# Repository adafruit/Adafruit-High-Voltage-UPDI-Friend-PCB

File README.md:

## Adafruit High Voltage UPDI Friend - USB Serial UPDI Programmer PCB

<a href="http://www.adafruit.com/products/5893"><br/>
Click here to purchase one from the Adafruit shop</a>

PCB files for the Adafruit High Voltage UPDI Friend - USB Serial UPDI Programmer. 

Format is EagleCAD schematic and board layout
* https://www.adafruit.com/product/5893

### Description

UPDI stands for Unified Program and Debug Interface, but this board is so smol and cute that we will call it the Unusually Playful Device Interfacer and pat its head when it does a good job. It's designed to make programming modern ATtiny chips very easy because it has 3V or 5V power and logic select, power, and transmit indicator LEDs, and a quick cable for poking into a breadboard.

Unlike our simple UPDI version, this board is HV for High Voltage because it will let you send a quick 12V pulse to the UPDI like right before programming. This is required for when the chip is configured to use the UPDI pin as a reset or GPIO. This board will also let you 'unbrick' any chip configured for HV usage, you can use it to reset the fuses for Low Voltage programming.

As for our seesaw boards, we have been working a lot with ATtiny816, ATtiny817, and ATtiny1616 chips lately. And we're often needing to program them with a CP2102-based breakout with a 1K resistor soldered between the RX and TX pins. But we were hankering for a nicer programmer!

This UPDI High Voltage Friend makes programming such chips very easy:

* Select between 3V or 5V power and logic - the 3V regulator can source up to 500mA to run even big projects. 
* Internal 12V boost converter with analog switch that will send a pulse to the UPDI line when the RTS pin is toggled low. 
* CH340E USB Serial converter chip with cross-platform drivers
* 1K Loop-back Resistor between RX and TX
* USB Type C for data and power connection to any computer
* JST SH cable included for quick plugging into a breadboard - you can get another JST SH 3-pin cable with sockets or with pin header here.
* 0.1" spaced breakout holes for custom connections.
* Green power OK LED
* Red serial activity LED
* Inspired by this [open-source hardware design](https://github.com/wagiminator/AVR-Programmer/tree/master/SerialUPDI_HV_Programmer) from [Stefan Wagner](https://github.com/wagiminator)!

We use Arduino IDE with the megaTinyCore board support package installed; simply select "Serial UPDI" as the programmer type. We use 230Kbps, but 56Kbps is also good. In order to enable the high-voltage fuses settings, you'll need to edit boards.txt to remove the # comment tag on the “UPDI/RESET PIN CONFIGURATION” lines.
### License

Adafruit invests time and resources providing this open source design, please support Adafruit and open-source hardware by purchasing products from [Adafruit](https://www.adafruit.com)!

Designed by Limor Fried/Ladyada for Adafruit Industries.

Creative Commons Attribution/Share-Alike, all text above must be included in any redistribution. 
See license.txt for additional details.

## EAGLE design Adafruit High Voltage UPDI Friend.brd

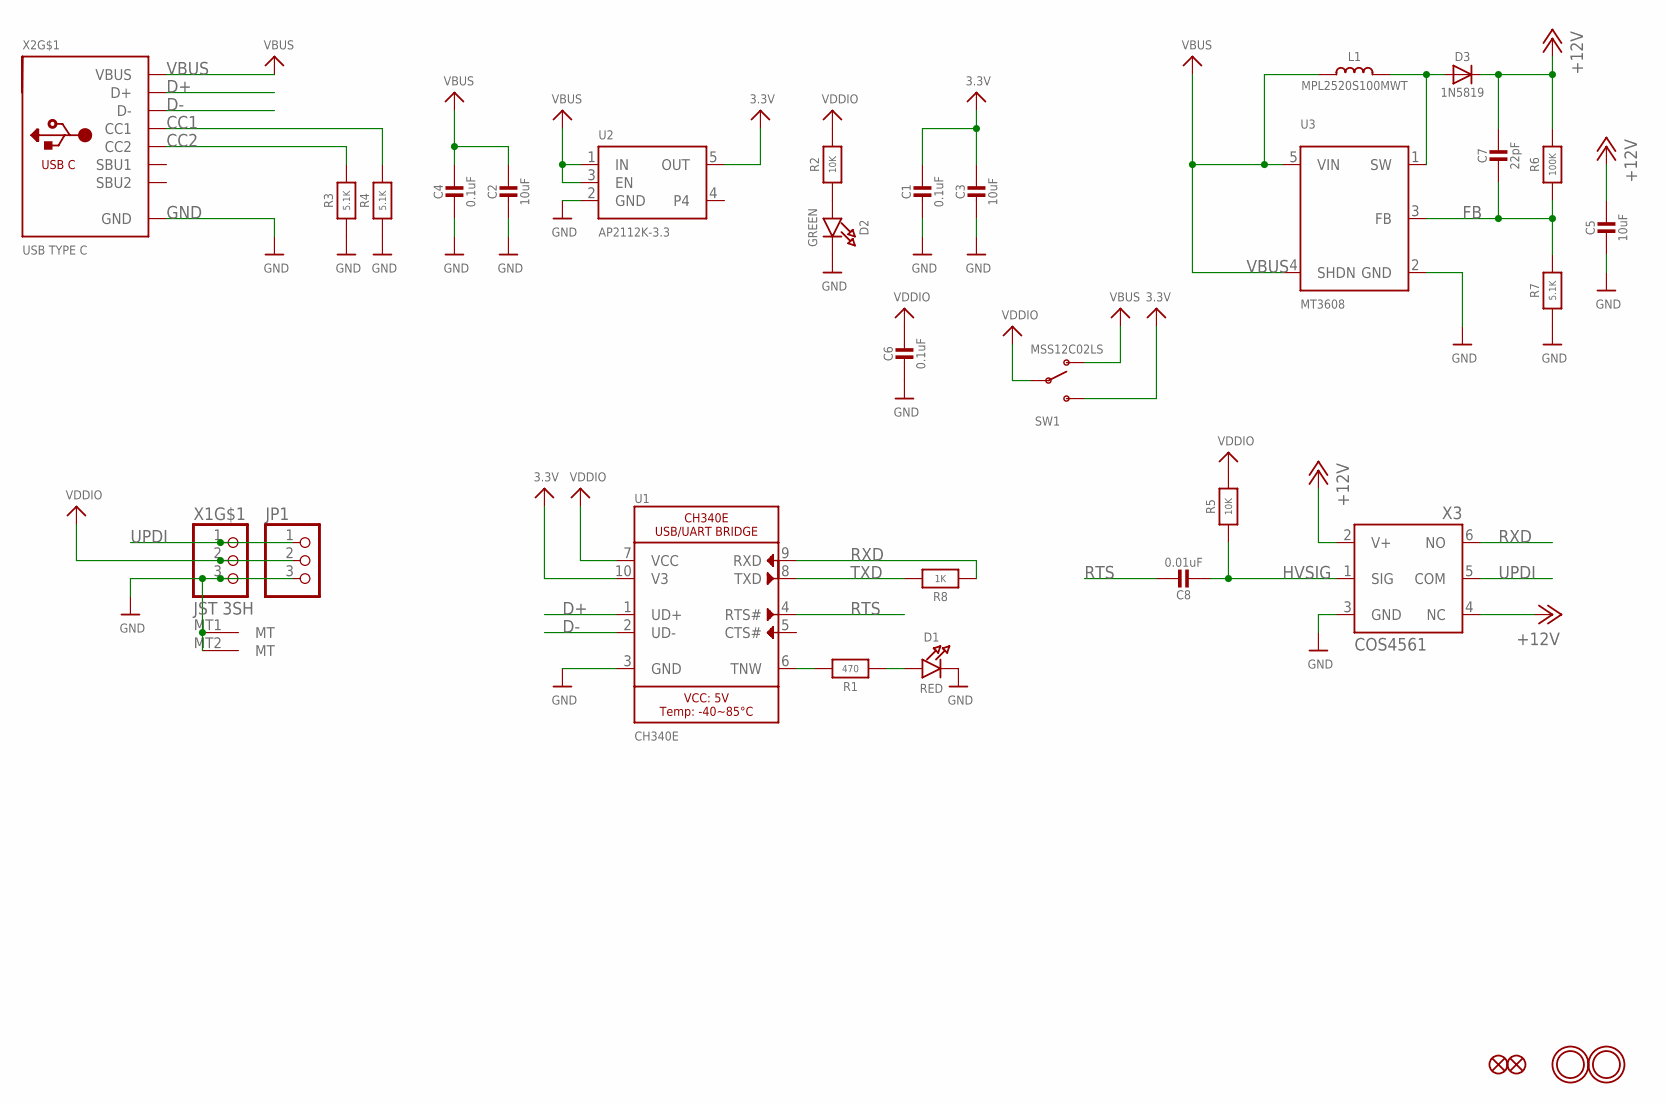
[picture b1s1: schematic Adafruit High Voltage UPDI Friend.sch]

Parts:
C1, C4, C6: 0.1uF; 0603-NO
C2, C3, C5: 10uF; 0805-NO
C7: 22pF; 0603-NO
C8: 0.01uF; 0603-NO
D1: RED; CHIPLED_0603_NOOUTLINE
D2: GREEN; CHIPLED_0603_NOOUTLINE
D3: 1N5819; SOD-323
FID1, FID2: FIDUCIAL_1MM
JP1: HEADER-1X376MIL; 1X03_ROUND_76
L1: MPL2520S100MWT; INDUCTOR_1007
R1: 470; 0603-NO
R2, R5: 10K; 0603-NO
R3, R4, R7: 5.1K; 0603-NO
R6: 100K; 0603-NO
R8: 1K; 0603-NO
SW1: MSS12C02LS; SPDT_SMT_SSSS811101
U1: CH340E; MSOP10
U2: AP2112K-3.3; SOT23-5; JLC_ROTATION 0
U3: MT3608; SOT23-6
U$18, U$19: MOUNTINGHOLE2.0; MOUNTINGHOLE_2.0_PLATED
X1: JST 3SH; JST_SH3
X2: USB TYPE C; USB_C_CUSB31-CFM2AX-01-X
X3: COS4561; SOT23-6

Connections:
3.3V: C1.1, C3.1, SW1.C (S), U1.10 (V3), U2.5 (OUT)
+12V: C5.1, C7.1, D3.C, R6.2, X3.2 (V+), X3.4 (NC)
CC1: R4.2, X2.A5 (CC1)
CC2: R3.2, X2.B5 (CC2)
D+: U1.1 (UD+), X2.A6 (D+), X2.B6 (D+)
D-: U1.2 (UD-), X2.A7 (D-), X2.B7 (D-)
FB: C7.2, R6.1, R7.2, U3.3 (FB)
GND: C1.2, C2.2, C3.2, C4.2, C5.2, C6.2, D1.C, D2.C, JP1.3, R3.1, R4.1, R7.1, U1.3 (GND), U2.2 (GND), U3.2 (GND), X1.3, X1.MT1 (MT), X1.MT2 (MT), X2.A1B12 (GND), X2.B1A12 (GND), X3.3 (GND)
HVSIG: C8.2, R5.1, X3.1 (SIG)
unnamed: D1.A, R1.1
unnamed: R1.2, U1.6 (TNW)
unnamed: D3.A, L1.P$2 (2), U3.1 (SW)
unnamed: D2.A, R2.1
RTS: C8.1, U1.4 (RTS#)
RXD: R8.2, U1.9 (RXD), X3.6 (NO)
TXD: R8.1, U1.8 (TXD)
UPDI: JP1.1, X1.1, X3.5 (COM)
VBUS: C2.1, C4.1, L1.P$1 (1), SW1.A (O), U2.1 (IN), U2.3 (EN), U3.4 (SHDN), U3.5 (VIN), X2.A4B9 (VBUS), X2.B4A9 (VBUS)
VDDIO: C6.1, JP1.2, R2.2, R5.2, SW1.B, U1.7 (VCC), X1.2

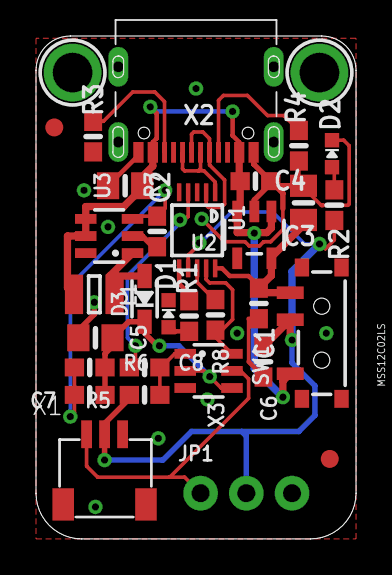
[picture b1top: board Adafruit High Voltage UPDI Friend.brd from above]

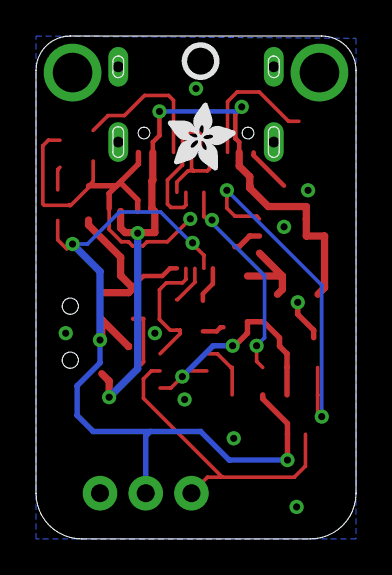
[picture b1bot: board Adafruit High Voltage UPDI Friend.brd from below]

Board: 2 copper layers, 17.8 x 27.9 mm, 46 parts (7 on the bottom side), 19 nets.

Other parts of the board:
PLABEL0: PLABEL0
PLABEL1: PLABEL1
PLABEL2: PLABEL2
PLABEL3: PLABEL3
PLABEL4: PLABEL4
PLABEL5: PLABEL5
PLABEL6: PLABEL6
PLABEL7: PLABEL7
PLABEL8: PLABEL8
PLABEL9: PLABEL9
PLABEL10: PLABEL10
PLABEL11: PLABEL11
U$17: PCBFEAT-REV-040
U$36: ADAFRUIT_3.5MM

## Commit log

2024-06-24 cookiecutter

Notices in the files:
parts and their libraries:
microbuilder: This work is placed in the public domain, and may be freely used for commercial and non-commercial work with the following conditions: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
